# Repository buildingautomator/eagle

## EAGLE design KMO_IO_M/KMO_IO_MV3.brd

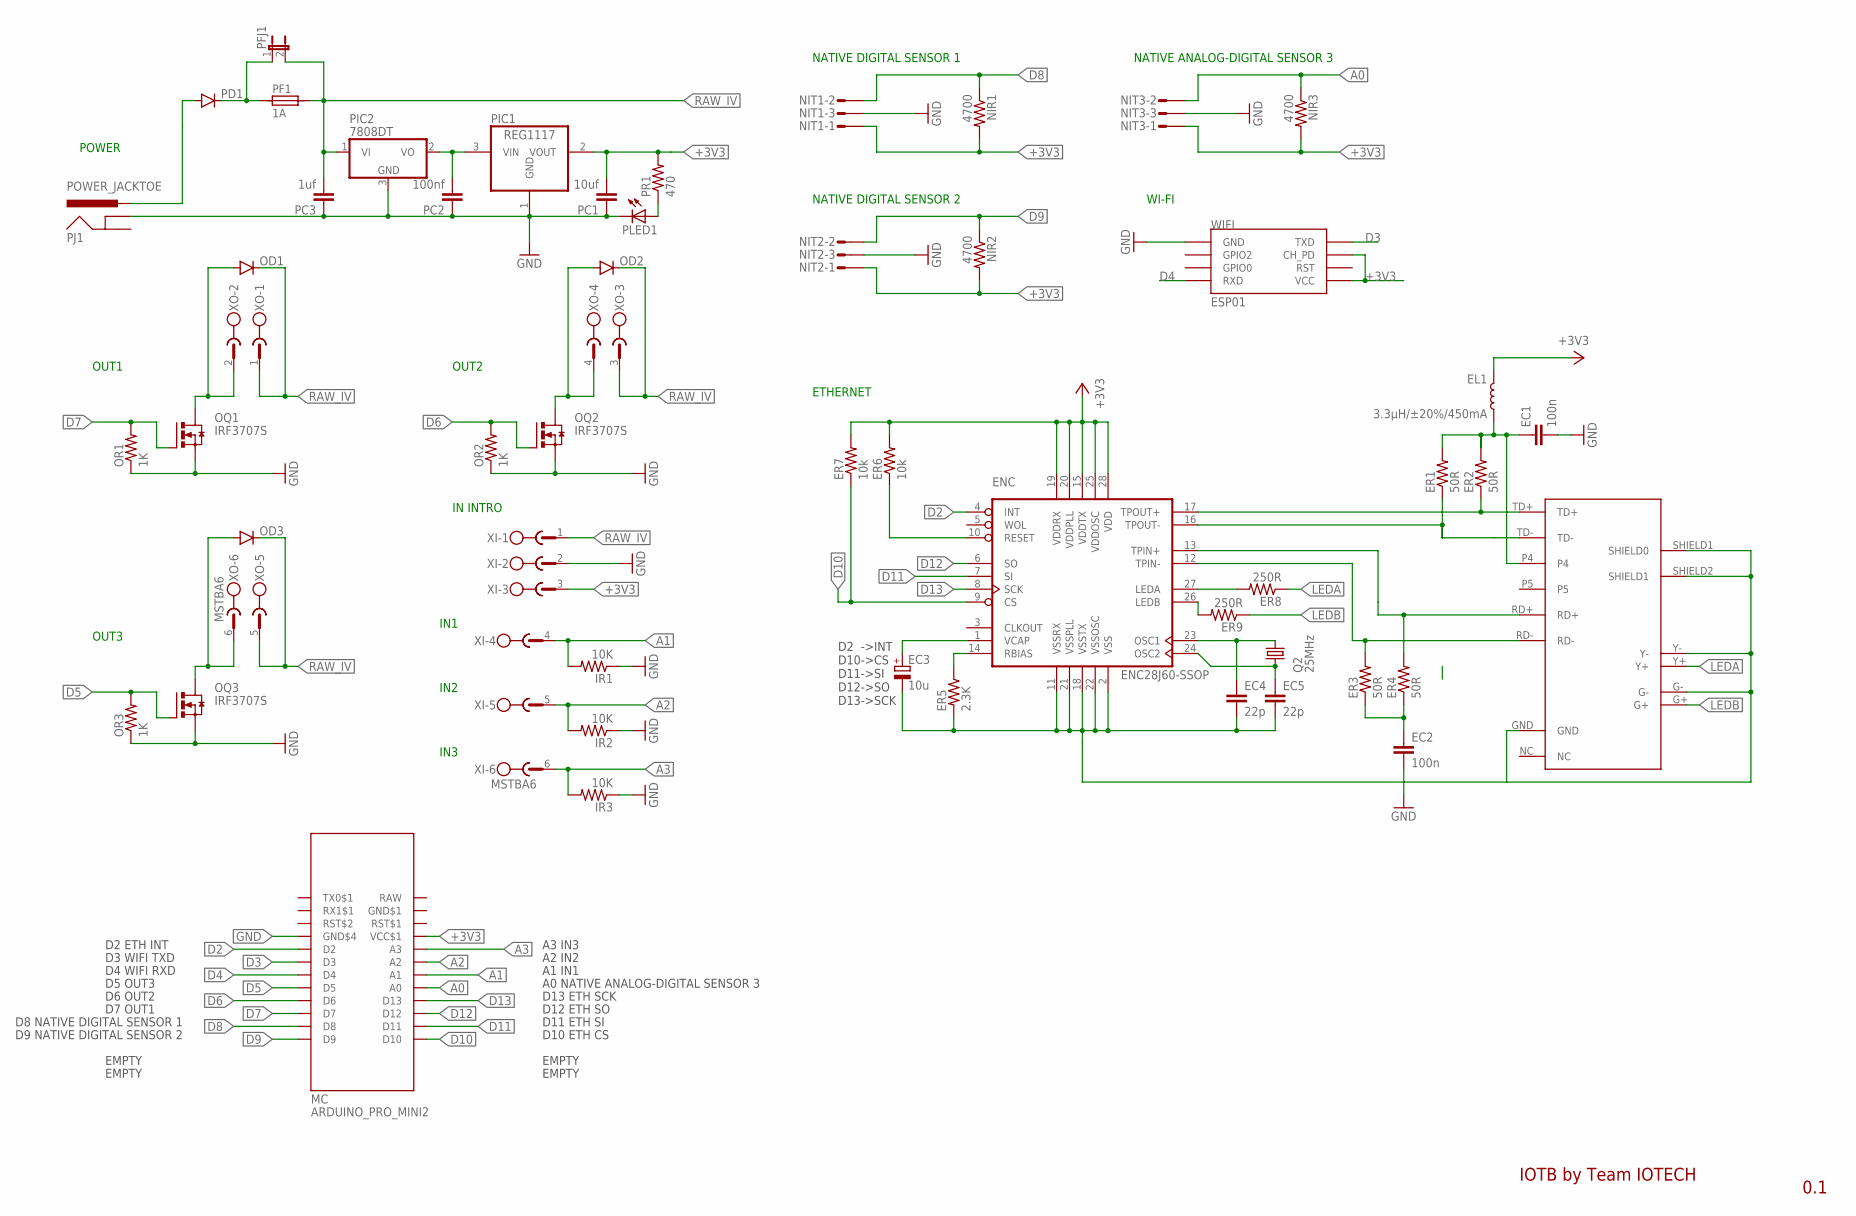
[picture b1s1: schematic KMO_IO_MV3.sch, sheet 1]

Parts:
EC1, EC2: 100n; 0805
EC3: 10u; SANYO-OSCON_SMD_B6
EC4, EC5: 22p; 0805
EL1: 3.3µH/±20%/450mA; 0805
ENC: ENC28J60-SSOP; SSOP28
ER1, ER2, ER3, ER4: 50R; 0805
ER5: 2.3K; 0805
ER6, ER7: 10k; 0805
ER8, ER9: 250R; 0805
IR1, IR2, IR3: 10K; 0805
MC: ARDUINO_PRO_MINI2
NIR1, NIR2, NIR3: 4700; 0805
NIT1, NIT2, NIT3: S03P
OD1, OD2, OD3: DIODESMA; SMA-DIODE
OQ1, OQ2, OQ3: IRF3707S; D2PACK
OR1, OR2, OR3: 1K; 0805
PC1: 10uf; 0805
PC2: 100nf; 0805
PC3: 1uf; 0805
PD1: DIODESMA; SMA-DIODE
PF1: 1A; 1820
PFJ1: JP1E; JP1
PIC1: REG1117; SOT223
PIC2: 7808DT; TO252
PJ1: POWER_JACKTOE; POWER_JACK_SMD_OVERPASTE_TOE
PLED1: LEDCHIP-LED0805; CHIP-LED0805
PR1: 470; 0805
Q2: 25MHz; HC49/S
U$2: HR911105A; RJ45
WIFI: ESP01
XI: MSTBA6
XO: MSTBA6

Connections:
+3V3: EL1.1, ENC.15 (VDDTX), ENC.19 (VDDRX), ENC.20 (VDDPLL), ENC.25 (VDDOSC), ENC.28 (VDD), ER6.2, ER7.2, MC.VCC$1, NIR1.2, NIR2.2, NIR3.2, NIT1.1, NIT2.1, NIT3.1, PC1.2, PIC1.2 (VOUT), PR1.2, WIFI.CH_PD, WIFI.VCC, XI.3
A0: MC.A0, NIR3.1, NIT3.2
A1: IR1.2, MC.A1, XI.4
A2: IR2.2, MC.A2, XI.5
A3: IR3.2, MC.A3, XI.6
D2: ENC.4 (INT), MC.D2
D3: MC.D3, WIFI.TX (TXD)
D4: MC.D4, WIFI.RX (RXD)
D5: MC.D5, OQ3.1 (G), OR3.2
D6: MC.D6, OQ2.1 (G), OR2.2
D7: MC.D7, OQ1.1 (G), OR1.2
D8: MC.D8, NIR1.1, NIT1.2
D9: MC.D9, NIR2.1, NIT2.2
D10: ENC.9 (CS), ER7.1, MC.D10
D11: ENC.7 (SI), MC.D11
D12: ENC.6 (SO), MC.D12
D13: ENC.8 (SCK), MC.D13
EP4: EC1.1, EL1.2, ER1.2, ER2.2, U$2.P4
GND: EC1.2, EC2.2, EC3.-, EC4.2, EC5.2, ENC.2 (VSS), ENC.11 (VSSRX), ENC.18 (VSSTX), ENC.21 (VSSPLL), ENC.22 (VSSOSC), ER5.2, IR1.1, IR2.1, IR3.1, MC.GND$4, NIT1.3, NIT2.3, NIT3.3, OQ1.3 (S), OQ2.3 (S), OQ3.3 (S), OR1.1, OR2.1, OR3.1, PC1.1, PC2.1, PC3.1, PIC1.1 (GND), PIC2.3 (GND), PJ1.GND (GNDBREAK), PLED1.C, U$2.G-, U$2.GND, U$2.SHIELD1 (SHIELD0), U$2.SHIELD2 (SHIELD1), U$2.Y-, WIFI.GND, XI.2
GND$1: MC.GDN$1 (GND$1)
LEDA: ER8.1, U$2.Y+
LEDB: ER9.1, U$2.G+
unnamed: OD3.A, OQ3.2 (D), XO.6
unnamed: PD1.C, PF1.1, PFJ1.1
unnamed: OD1.A, OQ1.2 (D), XO.2
unnamed: OD2.A, OQ2.2 (D), XO.4
unnamed: EC2.1, ER3.1, ER4.1
unnamed: PD1.A, PJ1.VIN0 (PWR)
unnamed: ENC.27 (LEDA), ER8.2
unnamed: PLED1.A, PR1.1
unnamed: PC2.2, PIC1.3 (VIN), PIC2.2 (VO)
unnamed: EC3.+, ENC.1 (VCAP)
unnamed: ENC.26 (LEDB), ER9.2
unnamed: ENC.10 (RESET), ER6.1
unnamed: ENC.14 (RBIAS), ER5.1
unnamed: EC5.1, ENC.24 (OSC2), Q2.1
unnamed: EC4.1, ENC.23 (OSC1), Q2.2
RAW: MC.RAW
RAW_IV: OD1.C, OD2.C, OD3.C, PC3.2, PF1.2, PFJ1.2, PIC2.1 (VI), XI.1, XO.1, XO.3, XO.5
RD+: ENC.13 (TPIN+), ER4.2, U$2.RD+
RD-: ENC.12 (TPIN-), ER3.2, U$2.RD-
TD+: ENC.17 (TPOUT+), ER2.1, U$2.TD+
TD-: ENC.16 (TPOUT-), ER1.1, U$2.TD-

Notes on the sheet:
POWER
OUT1
NATIVE DIGITAL SENSOR 1
IN INTRO
NATIVE DIGITAL SENSOR 2
OUT2
WI-FI
D2 ETH INT
D8 NATIVE DIGITAL SENSOR 1
D9 NATIVE DIGITAL SENSOR 2
EMPTY
A3 IN3
A2 IN2
A1 IN1
A0 NATIVE ANALOG-DIGITAL SENSOR 3
D13 ETH SCK
D12 ETH SO
D11 ETH SI
D10 ETH CS
OUT3
D4 WIFI RXD
D3 WIFI TXD
D7 OUT1
D6 OUT2
D5 OUT3
NATIVE ANALOG-DIGITAL SENSOR 3
IN1
IN2
IN3
IOTB by Team IOTECH
0.1
ETHERNET
D2 ->INT D10->CS D11->SI D12->SO D13->SCK

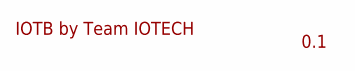
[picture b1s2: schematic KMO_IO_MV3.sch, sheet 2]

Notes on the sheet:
IOTB by Team IOTECH
0.1

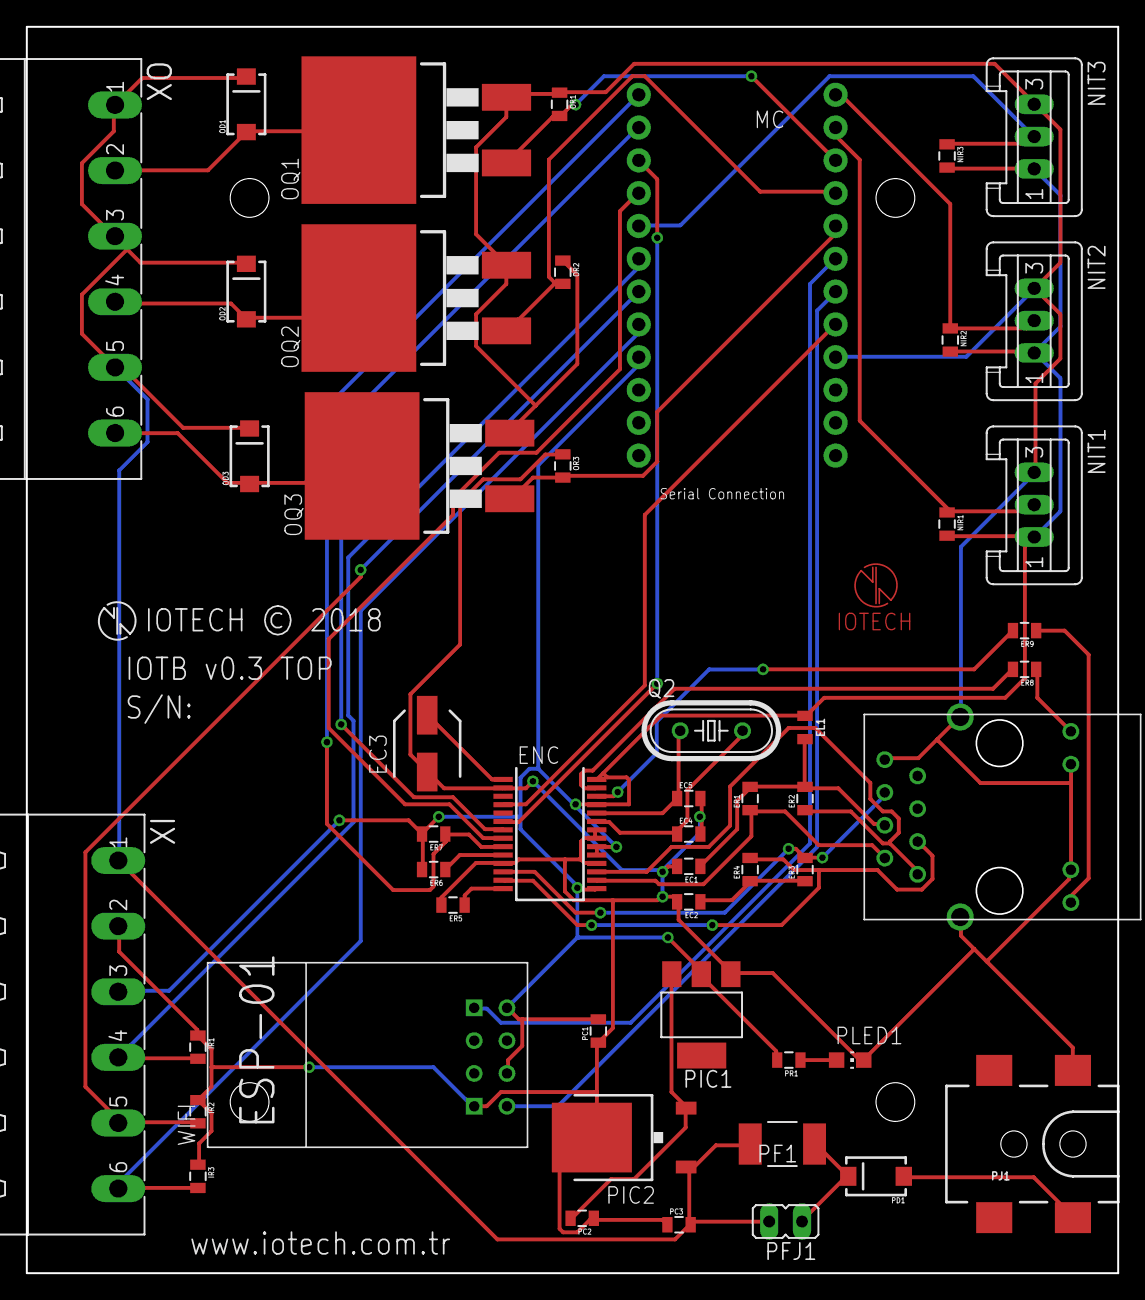
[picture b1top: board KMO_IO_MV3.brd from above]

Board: 2 copper layers, 84.5 x 96.5 mm, 52 parts (0 on the bottom side), 41 nets.

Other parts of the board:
U$1: IOTECH_COPPER_W_TEXT

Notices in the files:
KMO_IO_M/KMO_IO_MV3.brd:
IOTECH © 2018
parts and their libraries:
SparkFun-Capacitors: Licensing: Creative Commons ShareAlike 4.0 International - https://creativecommons.org/licenses/by-sa/4.0
